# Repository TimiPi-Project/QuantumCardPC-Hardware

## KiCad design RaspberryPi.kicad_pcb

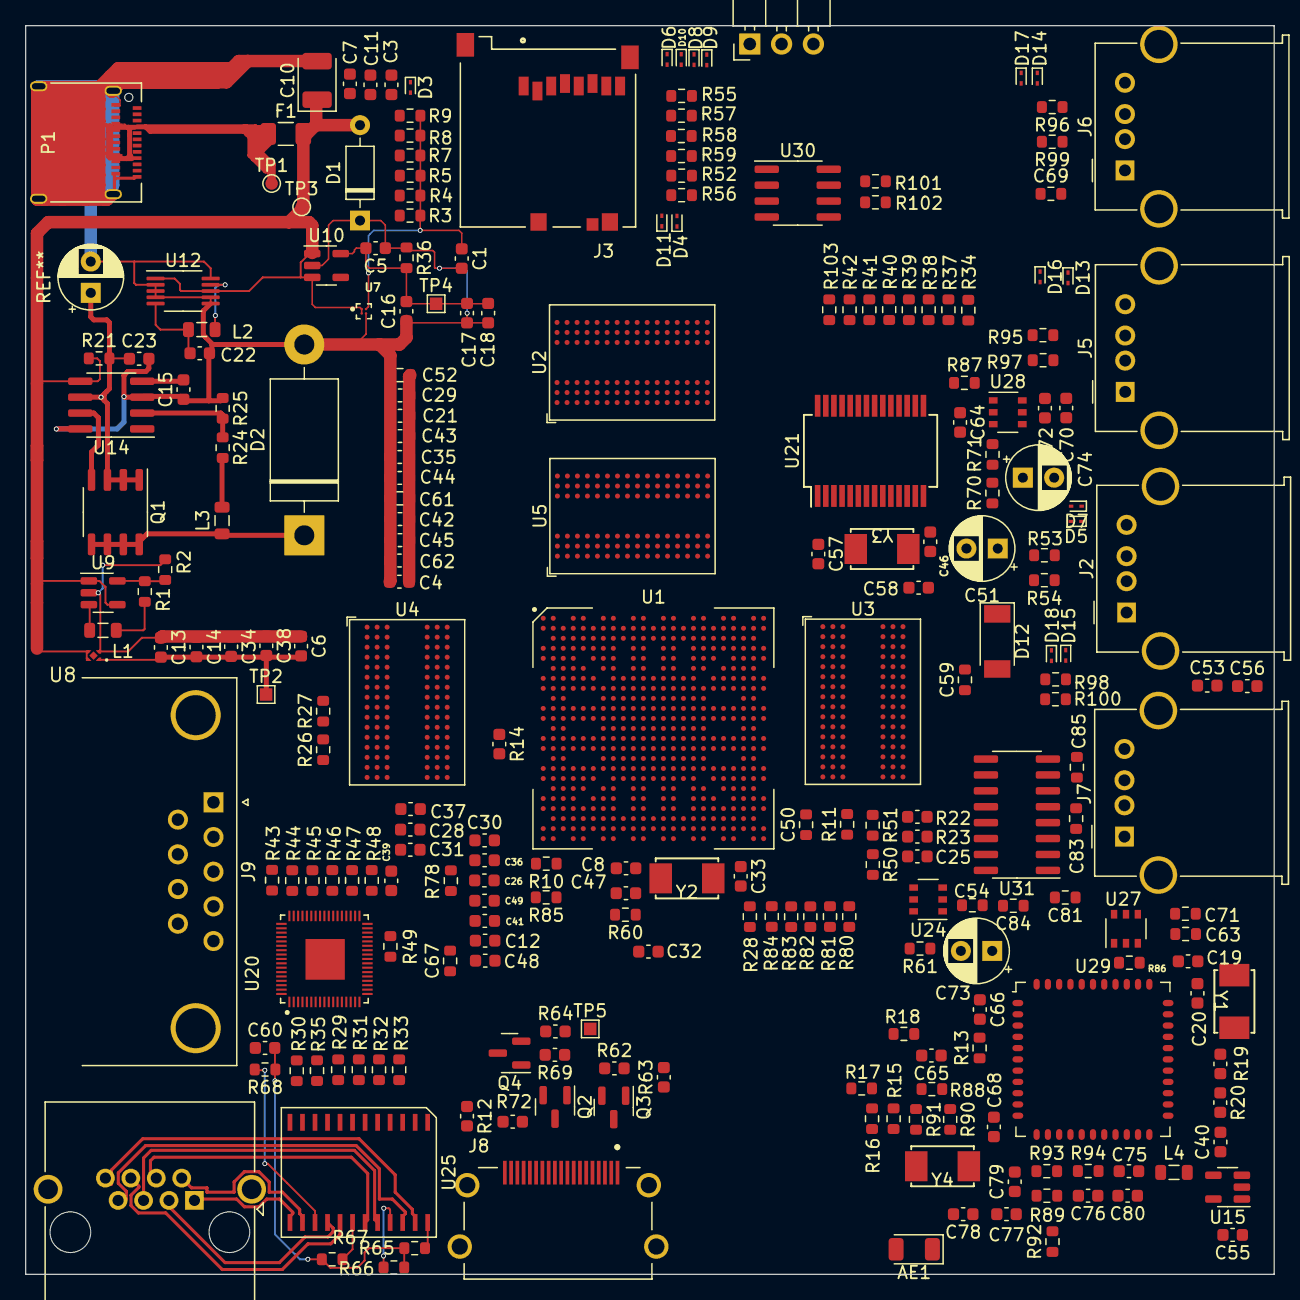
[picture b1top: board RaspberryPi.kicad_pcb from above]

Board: 4 copper layers, 99.7 x 99.7 mm, 244 parts (0 on the bottom side), 252 nets.

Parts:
AE1: Antenna; Johanson_2450AT18x100
C1, C4, C5, C6, C13, C17, C21, C23, C30, C31, C35, C36, C39, C40, C42, C43, C44, C45, C47, C49, C53, C64: 100nF; C_0603_1608Metric
C3, C34, C46, C48, C56: 1uF; C_0603_1608Metric
C7: 4.7uF; C_0603_1608Metric
C8, C18, C26, C28, C38, C55: 10nF; C_0603_1608Metric
C10: 47uF; CP_EIA-3528-21_Kemet-B
C11, C12, C16, C29, C62, C70: 10uF; C_0603_1608Metric
C14, C25, C41, C60: 1nF; C_0603_1608Metric
C15, C72: 0.1uF; C_0603_1608Metric
C19, C20, C57, C58: 22pF; C_0603_1608Metric
C22, C37: 22uF; C_0603_1608Metric
C32, C33: 12pF; C_0603_1608Metric
C50, C54, C63, C81, C83, C84, C85: 100nF; R_0603_1608Metric
C51, C73, C74: CP_Radial_D5.0mm_P2.50mm
C52, C59, C61, C69: 10uF; R_0603_1608Metric
C65, C68, C75, C76, C77, C78, C79, C80: 18pF; C_0603_1608Metric
C66: 10pF; C_0603_1608Metric
C67: 22pF; R_0603_1608Metric
C71: 0.1uF; R_0603_1608Metric
D1: SMBJ5.0A; D_DO-35_SOD27_P7.62mm_Horizontal
D2: 1N5820; D_DO-201AD_P15.24mm_Horizontal
D3, D4, D5, D6, D7, D8, D9, D10, D11, D13, D14, D15, D16, D17, D18: ESD9B5VL; D_SOD-923
D12: PMEG3030BEP; D_SOD-128
F1: 5A; Fuse_1206_3216Metric
J1: DBG1; PinHeader_1x03_P2.54mm_Horizontal
J2, J5, J6, J7: USB_A; USB_A_Molex_67643_Horizontal
J3: Micro_SD_Card_Det; MOLEX_47352-1001
J4: RJ45; RJ45_Amphenol_RJHSE5380
J8: HDMI_A; AMPHENOL_10029449-001RLF
J9: DB9_Male; DSUB-9_Male_Horizontal_P2.77x2.84mm_EdgePinOffset7.70mm_Hou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
L1: 2.2uH; L_0805_2012Metric
L2: 10uH; L_0805_2012Metric
L3: 47uH; L_0805_2012Metric
L4: 3.3uH; L_0805_2012Metric
P1: USB_C_Plug_USB2.0; USB_C_Receptacle_Amphenol_12401610E4-2A
Q1: Si9430; SO-8_3.9x4.9mm_P1.27mm
Q2, Q3, Q4: 2N7002; SOT-23
R1, R40: 100K; R_0603_1608Metric
R2: 120K; R_0603_1608Metric
R3, R4, R5, R7, R8, R9, R10, R13, R15, R16, R17, R18, R27, R34, R38, R39, R41, R42, R50, R60, R70, R71, R101: 10K; R_0603_1608Metric
R11: 133R; R_0603_1608Metric
R12, R22, R23: 1K; C_0603_1608Metric
R14: 1.62K; C_0603_1608Metric
R19, R62: 10K; C_0603_1608Metric
R20: 22R; C_0603_1608Metric
R21: 0.05R; R_0603_1608Metric
R24: 180K; R_0603_1608Metric
R25: 150K; R_0603_1608Metric
R26: 6.8K; R_0603_1608Metric
R28: 1M; R_0603_1608Metric
R29, R30, R31, R32, R33, R35, R44, R45, R46, R47, R49: 4K7; R_0603_1608Metric
R36: 510R; R_0603_1608Metric
R37: 680R; R_0603_1608Metric
R43: 2.49K; R_0603_1608Metric
R48: 1K5; R_0603_1608Metric
R51: 15K; R_0603_1608Metric
R52, R55, R56, R57, R58, R59, R89, R90, R91, R92, R93, R94: 22R; R_0603_1608Metric
R53, R54, R95, R96, R97, R98, R99, R100: 90; R_0603_1608Metric
R61, R86, R87: 20K; R_0603_1608Metric
R63, R64: 4.7K; C_0603_1608Metric
R65, R66, R67, R68: 75; R_0603_1608Metric
R69, R72: 1.5K; C_0603_1608Metric
R78, R80, R81, R82, R83, R84, R85: 22; R_0603_1608Metric
R88: 100R; R_0603_1608Metric
R102, R103: 2.2K; R_0603_1608Metric
TP1, TP3: +5; TestPoint_Pad_D1.0mm
TP2: 1V_USB; TestPoint_Pad_1.0x1.0mm
TP4: 1V8_USB; TestPoint_Pad_1.0x1.0mm
TP5: 3V3_IO; TestPoint_Pad_1.0x1.0mm
U1: RK3368; TFBGA453
U2, U3, U4, U5: MT41KxxxM16TW; BGA-96_9.0x13.0mm_Layout2x3x16_P0.8mm
U7: TPS7A21; BGA4N35P2X2_64X64X33
U8: TPS7A0310; SUP_TPS3831L30DQNR
U9: TLV62565-LibCool; SOT-23-5
U10: TPS72118; SOT-23-5
U12: TPS62052DGS; VSSOP-10_3x3mm_P0.5mm
U14: MAX1651; SOIC-8_3.9x4.9mm_P1.27mm
U15: SN74LVC1G14DBV; SOT-23-5
U20: RTL8211E-VB-CG; QFN35P700X700X80-69N
U21: GL852G; SSOP-28_5.3x10.2mm_P0.65mm
U24, U27, U28: MP65151DJ; TSOP-6_1.65x3.05mm_P0.95mm
U25: GST5009; SOIC-24
U29: AP6335
U30: AT24C16B; SOIC-8_3.9x4.9mm_P1.27mm
U31: MAX3232; SOIC-16_3.9x9.9mm_P1.27mm
Y1: 32.768kHz; OSC_5032
Y2: 24MHz; OSC_5032
Y3: 12MHz; OSC_5032
Y4: 37.4MHz; OSC_5032

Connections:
+1V0: C6.2, C12.2, C13.2, C14.2, C26.2, C30.2, C34.2, C36.2, C38.2, C41.2, C48.2, C49.2, TP2.1, U1.G13 (PLL_VDD_1), U1.N7, U1.R7, U1.V21, U1.W7, U1.W8, U1.Y8, U1.Y21, U8.1 (OUT), U20.3 (VDD10), U20.9 (VDD10), U20.28 (VDD10), U20.36 (VDD10), U20.40 (VDD10)
+1V1: L1.1, R1.2, U1.E18, U1.G8, U1.G10, U1.G12, U1.G14, U1.G16, U1.J17, U1.M17, U1.N8, U1.T16, U1.T17, U1.U9, U1.U10, U1.U11, U1.U12, U1.U13, U1.U14, U1.U15, U1.U16, U1.V10, U1.V11, U1.V13, U1.V14, U1.V16, U1.W10, U1.W11, U1.W13, U1.W14, U1.W16, U1.Y13, U1.Y14
+1V5: C22.2, L2.2, U12.5 (FB)
+1V8: C5.2, C16.2, C17.2, C18.2, R10.2, R36.2, TP4.1, U1.N6, U1.T7, U1.V20, U1.Y10, U10.5 (OUT)
+3.3VP: C1.1, R3.2, R4.2, R5.2, R7.2, R8.2, R9.2, U7.A2 (OUT)
+3V3: C4.2, C21.2, C29.2, C35.2, C39.2, C42.2, C43.2, C44.2, C45.2, C52.2, C61.2, C62.2, J3.4 (VDD), L3.2, Q2.1 (G), Q3.1 (G), Q4.1 (G), R13.2, R15.2, R16.2, R17.2, R18.2, R19.2, R24.2, R30.1, R34.2, R35.1, R39.1, R40.1, R41.1, R42.1, R44.2, R45.2, R46.2, R47.2, R48.2, R49.1, R62.2, R63.2, R64.2, R101.1, R102.1, R103.1, TP5.1, U1.K17, U1.P17, U1.T4, U1.T5, U1.T6, U15.5 (VCC), U20.6 (VDD33), U20.15 (VDD33), U20.21 (VDD33), U20.37 (VDD33), U20.38 (ENSWREG), U20.41 (VDD33), U20.44 (VDD33), U20.45 (VDD33), U21.1 (AVDD1), U21.5 (AVDD2), U21.10 (AVDD3), U21.16 (DVDD), U21.24 (V33), U24.1 (IN), U27.1 (IN), U28.1 (IN), U29.9 (VBat), U29.22 (VDDIO), U30.8 (VCC), U31.16 (VCC)
+5V: C3.1, C7.2, C10.1, C11.1, D1.2 (A), F1.2, J8.18 (+5V), R21.1, R50.2, R69.2, R72.2, TP3.1, U7.A1 (IN), U7.B1 (EN), U8.3 (EN), U8.4 (IN), U9.1 (EN), U9.4 (VIN), U10.1 (IN), U10.3 (EN), U12.1 (VIN), U12.8 (EN), U14.5 (V+)
/32K_IN: C40.2, R20.2, U1.AA9, U15.2, U15.4, U29.24 (LPO)
/A0: U1.A11 (A0), U2.N3 (A0), U3.N3 (A0), U4.N3 (A0), U5.N3 (A0)
/A1: U1.C12 (A1), U2.P7 (A1), U3.P7 (A1), U4.P7 (A1), U5.P7 (A1)
/A2: U1.B12 (A2), U2.P3 (A2), U3.P3 (A2), U4.P3 (A2), U5.P3 (A2)
/A3: U1.E13 (A3), U2.N2 (A3), U3.N2 (A3), U4.N2 (A3), U5.N2 (A3)
/A4: U1.C13 (A4), U2.P8 (A4), U3.P8 (A4), U4.P8 (A4), U5.P8 (A4)
/A5: U1.A14 (A5), U2.P2 (A5), U3.P2 (A5), U4.P2 (A5), U5.P2 (A5)
/A6: U1.B14 (A6), U2.R8 (A6), U3.R8 (A6), U4.R8 (A6), U5.R8 (A6)
/A7: U1.C14 (A7), U2.R2 (A7), U3.R2 (A7), U4.R2 (A7), U5.R2 (A7)
/A8: U1.D14 (A8), U2.T8 (A8), U3.T8 (A8), U4.T8 (A8), U5.T8 (A8)
/A9: U1.E14 (A9), U2.R3 (A9), U3.R3 (A9), U4.R3 (A9), U5.R3 (A9)
/A10: U1.C15 (A10), U2.L7 (A10/AP), U3.L7 (A10/AP), U4.L7 (A10/AP), U5.L7 (A10/AP)
/A11: U1.B15 (A11), U2.R7 (A11), U3.R7 (A11), U4.R7 (A11), U5.R7 (A11)
/A12: U1.D18 (A12), U2.N7 (A12/~BC), U3.N7 (A12/~BC), U4.N7 (A12/~BC), U5.N7 (A12/~BC)
/A13: U1.C16 (A13), U2.T3 (A13), U3.T3 (A13), U4.T3 (A13), U5.T3 (A13)
/A14: U1.B16 (A14), U2.T7 (A14), U3.T7 (A14), U4.T7 (A14), U5.T7 (A14)
/BA0: U1.D11 (BA0), U2.M2 (BA0), U3.M2 (BA0), U4.M2 (BA0), U5.M2 (BA0)
/BA1: U1.C11 (BA1), U2.N8 (BA1), U3.N8 (BA1), U4.N8 (BA1), U5.N8 (BA1)
/BA2: U1.B11 (BA2), U2.M3 (BA2), U3.M3 (BA2), U4.M3 (BA2), U5.M3 (BA2)
/CASN: U1.B10 (CASN), U2.K3 (~CAS), U3.K3 (~CAS), U4.K3 (~CAS), U5.K3 (~CAS)
/CEC: J8.13 (CEC), Q2.3 (D)
/CKE0: U1.C9 (CKE0), U2.K9 (CKE), U3.K9 (CKE), U4.K9 (CKE), U5.K9 (CKE)
/CLK: U1.B13 (DDRCLK), U2.J7 (CK), U3.J7 (CK), U4.J7 (CK), U5.J7 (CK)
/CLKN: U1.A13 (DDRCLKN), U2.K7 (~CK), U3.K7 (~CK), U4.K7 (~CK), U5.K7 (~CK)
/CS0N: U1.A8 (CS0N), U3.L2 (~CS), U5.L2 (~CS)
/CS1N: U1.B9 (CS1N), U2.L2 (~CS), U4.L2 (~CS)
/D0: U1.E22 (DQ0), U2.F7 (DQ1), U3.E3 (DQ0)
/D1: U1.D21 (DQ1), U3.F7 (DQ1)
/D2: U1.C22 (DQ2), U2.F8 (DQ3), U3.F2 (DQ2)
/D3: U1.D22 (DQ3), U2.F2 (DQ2), U3.F8 (DQ3)
/D4: U1.A23 (DQ4), U2.H7 (DQ7), U3.H3 (DQ4)
/D5: U1.B23 (DQ5), U3.H8 (DQ5)
/D6: U1.D23 (DQ6), U2.H8 (DQ5), U3.G2 (DQ6)
/D7: U1.E23 (DQ7), U2.H3 (DQ4), U3.H7 (DQ7)
/D8: U1.D6 (DQ8), U4.F7 (DQ1), U5.E3 (DQ0)
/D9: U1.C6 (DQ9), U4.E3 (DQ0), U5.F7 (DQ1)
/D10: U1.B6 (DQ10), U4.F8 (DQ3), U5.F2 (DQ2)
/D11: U1.E7 (DQ11), U4.F2 (DQ2), U5.F8 (DQ3)
/D12: U1.C7 (DQ12), U4.H7 (DQ7), U5.H3 (DQ4)
/D13: U1.E8 (DQ13), U4.G2 (DQ6), U5.H8 (DQ5)
/D14: U1.D8 (DQ14), U4.H8 (DQ5), U5.G2 (DQ6)
/D15: U1.C8 (DQ15), U4.H3 (DQ4), U5.H7 (DQ7)
/D16: U1.C18 (DQ16), U2.C3 (DQ9), U3.D7 (DQ8)
/D17: U1.B17 (DQ17), U2.D7 (DQ8), U3.C3 (DQ9)
/D18: U1.A17 (DQ18), U2.C2 (DQ11), U3.C8 (DQ10)
/D19: U1.A20 (DQ19), U2.C8 (DQ10), U3.C2 (DQ11)
/D20: U1.C19 (DQ20), U2.A3 (DQ15), U3.A7 (DQ12)
/D21: U1.B18 (DQ21), U2.B8 (DQ14), U3.A2 (DQ13)
/D22: U1.B20 (DQ22), U2.A2 (DQ13), U3.B8 (DQ14)
/D23: U1.B21 (DQ23), U2.A7 (DQ12), U3.A3 (DQ15)
/D24: U1.B2 (DQ24), U4.C3 (DQ9), U5.D7 (DQ8)
/D25: U1.B3 (DQ25), U4.D7 (DQ8), U5.C3 (DQ9)
/D26: U1.C3 (DQ26), U4.C2 (DQ11), U5.C8 (DQ10)
/D27: U1.C4 (DQ27), U4.C8 (DQ10), U5.C2 (DQ11)
/D28: U1.D5 (DQ28), U4.A3 (DQ15), U5.A7 (DQ12)
/D29: U1.C5 (DQ29), U4.B8 (DQ14), U5.A2 (DQ13)
/D30: U1.B5 (DQ30), U4.A2 (DQ13), U5.B8 (DQ14)
/D31: U1.A5 (DQ31), U4.A7 (DQ12), U5.A3 (DQ15)
/DDCSCL: J8.15 (SCL), Q3.3 (D), R69.1
/DDCSDA: J8.16 (SDA), Q4.3 (D), R72.1
/DDRPWR: C28.2, C31.2, C37.2, R22.2, U1.E16 (VDD9), U1.E17 (VDD10), U1.F7 (VDD1), U1.F8 (VDD2), U1.F10 (VDD3), U1.F11 (VDD4), U1.F13 (VDD5), U1.F14 (VDD6), U1.F16 (VDD7), U1.F17 (VDD8), U2.A1 (VDDQ), U2.A8 (VDDQ), U2.B2 (VDD), U2.C1 (VDDQ), U2.C9 (VDDQ), U2.D2 (VDDQ), U2.D9 (VDD), U2.E9 (VDDQ), U2.F1 (VDDQ), U2.G7 (VDD), U2.H1 (VREFDQ), U2.H2 (VDDQ), U2.H9 (VDDQ), U2.K2 (VDD), U2.K8 (VDD), U2.M8 (VREFCA), U2.N1 (VDD), U2.N9 (VDD), U2.R1 (VDD), U2.R9 (VDD), U3.A1 (VDDQ), U3.A8 (VDDQ), U3.B2 (VDD), U3.C1 (VDDQ), U3.C9 (VDDQ), U3.D2 (VDDQ), U3.D9 (VDD), U3.E9 (VDDQ), U3.F1 (VDDQ), U3.G7 (VDD), U3.H1 (VREFDQ), U3.H2 (VDDQ), U3.H9 (VDDQ), U3.K2 (VDD), U3.K8 (VDD), U3.M8 (VREFCA), U3.N1 (VDD), U3.N9 (VDD), U3.R1 (VDD), U3.R9 (VDD), U4.A1 (VDDQ), U4.A8 (VDDQ), U4.B2 (VDD), U4.C1 (VDDQ), U4.C9 (VDDQ), U4.D2 (VDDQ), U4.D9 (VDD), U4.E9 (VDDQ), U4.F1 (VDDQ), U4.G7 (VDD), U4.H1 (VREFDQ), U4.H2 (VDDQ), U4.H9 (VDDQ), U4.K2 (VDD), U4.K8 (VDD), U4.M8 (VREFCA), U4.N1 (VDD), U4.N9 (VDD), U4.R1 (VDD), U4.R9 (VDD), U5.A1 (VDDQ), U5.A8 (VDDQ), U5.B2 (VDD), U5.C1 (VDDQ), U5.C9 (VDDQ), U5.D2 (VDDQ), U5.D9 (VDD), U5.E9 (VDDQ), U5.F1 (VDDQ), U5.G7 (VDD), U5.H1 (VREFDQ), U5.H2 (VDDQ), U5.H9 (VDDQ), U5.K2 (VDD), U5.K8 (VDD), U5.M8 (VREFCA), U5.N1 (VDD), U5.N9 (VDD), U5.R1 (VDD), U5.R9 (VDD)
/DDR_RST: U1.E11 (RESETN), U2.T2 (~RESET), U3.T2 (~RESET), U4.T2 (~RESET), U5.T2 (~RESET)
/DM0: U1.D20 (DM0), U2.E7 (LDM), U3.E7 (LDM)
/DM1: U1.E6 (DM1), U4.E7 (LDM), U5.E7 (LDM)
/DM2: U1.C20 (DM2), U2.D3 (UDM), U3.D3 (UDM)
/DM3: U1.A2 (DM3), U4.D3 (UDM), U5.D3 (UDM)
/DQS0M: U1.A22 (DQS0N), U2.G3 (~LDQS), U3.G3 (~LDQS)
/DQS0P: U1.B22 (DQS0), U2.F3 (LDQS), U3.F3 (LDQS)
/DQS1M: U1.A7 (DQS1N), U4.G3 (~LDQS), U5.G3 (~LDQS)
/DQS1P: U1.B7 (DQS1), U4.F3 (LDQS), U5.F3 (LDQS)
/DQS2M: U1.A19 (DQS2N), U2.B7 (~UDQS), U3.B7 (~UDQS)
/DQS2P: U1.B19 (DQS2), U2.C7 (UDQS), U3.C7 (UDQS)
/DQS3M: U1.A4 (DQS3N), U4.B7 (~UDQS), U5.B7 (~UDQS)
/DQS3P: U1.B4 (DQS3), U4.C7 (UDQS), U5.C7 (UDQS)
/HDMICEC: Q2.2 (S), R62.1, U1.U23
/HDMITXC+: J8.10 (CK+), U1.AB1
/HDMITXC-: J8.12 (CK-), U1.AC1
/HDMITXD0+: J8.7 (D0+), U1.AB2
/HDMITXD0-: J8.9 (D0-), U1.AC2
/HDMITXD1+: J8.4 (D1+), U1.AB4
/HDMITXD1-: J8.6 (D1-), U1.AC4
/HDMITXD2+: J8.1 (D2+), U1.AB5
/HDMITXD2-: J8.3 (D2-), U1.AC5
/HDMI_HPD: J8.19 (HPD), R12.2
/HOST1_D+: U1.AB23, U21.26 (DP0)
/HOST1_D-: U1.AC23, U21.25 (DM0)
/HOST_PWR1: C70.2, C72.2, C74.1, J5.1 (VBUS), U28.6 (OUT)
/HOST_PWR2: C69.2, C71.2, C73.1, J6.1 (VBUS), J7.1 (VBUS), U27.6 (OUT)
/HOST_VBus: R70.1, R71.1, U1.AA8
/HUB_D2+: R96.2, U21.3 (DP2)
/HUB_D2-: R99.2, U21.2 (DM2)
/HUB_D3+: R95.2, U21.9 (DP3)
/HUB_D3-: R97.2, U21.8 (DM3)
/I2C2_SCL: R102.2, U1.F20, U30.6 (SCL)
/I2C2_SDA: R103.2, U1.E20, U30.5 (SDA)
/I2C5_SCL_HDMI: Q3.2 (S), R63.1, U1.T23
/I2C5_SDA_HDMI: Q4.2 (S), R64.1, U1.T22
/MAC_MDIO: R48.1, U20.31 (MAC_MDIO)
/MDI0+: U20.1 (MDI0+), U25.12 (TD4-)
/MDI0-: U20.2 (MDI0-), U25.11 (TD4+)
/MDI1+: U20.4 (MDI1+), U25.9 (TD3-)
/MDI1-: U20.5 (MDI1-), U25.8 (TD3+)
/MDI2+: U20.7 (MDI2+), U25.6 (TD2-)
/MDI2-: U20.8 (MDI2-), U25.5 (TD2+)
/MDI3+: U20.10 (MDI3+), U25.3 (TD1-)
/MDI3-: U20.11 (MDI3-), U25.2 (TD1+)
/ODT0: U1.D17 (ODT0), U3.K1 (ODT), U5.K1 (ODT)
/ODT1: U1.C17 (ODT1), U2.K1 (ODT), U4.K1 (ODT)
/OTGVDD: C59.2, D12.2 (A), U24.6 (OUT)
/OTG_D+: R53.2, U1.AB22
/OTG_D-: R54.2, U1.AC22
/OTG_DET: C50.2, R50.1, R51.2, U1.AA21
/OTG_VBus: R60.1, U1.AB14
/PHY_CLKOUT125: C67.2, R78.2, U20.46 (CLK125)
/PHY_INT: R35.2, U20.20 (INTB)
/PHY_PMEB: R49.2, U20.33 (PHY_PMEB)
/PHY_RXD0: R30.2, U20.14 (RXD0)
/PHY_RXD1: R31.2, U20.16 (RXD1)
/PHY_RXD2: R32.2, U20.17 (RXD2)
/PHY_RXD3: R33.2, U20.18 (RXD3)
/PHY_RXDV: R29.2, U20.13 (RXCTL)
/PHY_TXCLK: R80.2, U20.22 (TXC)
/PHY_TXD0: R44.1, R81.2, U20.23 (TXD0)
/PHY_TXD1: R45.1, R82.2, U20.24 (TXD1)
/PHY_TXD2: R46.1, R83.2, U20.25 (PHY_TXD2)
/PHY_TXD3: R47.1, R84.2, U20.26 (PHY_TXD3)
/PHY_TXEN: R85.2, U20.27 (PHY_TXEN)
/RASN: U1.A10 (RASN), U2.J3 (~RAS), U3.J3 (~RAS), U4.J3 (~RAS), U5.J3 (~RAS)
/RECOVER: C8.2, R10.1, U1.AC11
/RSET: R43.1, U20.39 (RSET)
/RST: C47.1, U1.AC8
/SDIO0_CLK: R92.1, U1.L19
/SDIO0_CMD: R18.1, R91.1, U1.L21
/SDIO0_D0: R13.1, R93.1, U1.M22
/SDIO0_D1: R15.1, R94.1, U1.N20
/SDIO0_D2: R16.1, R89.1, U1.N23
/SDIO0_D3: R17.1, R90.1, U1.L20
/SDMMC_CLK: R57.1, U1.N22
/SDMMC_CMD: R8.1, R55.1, U1.N19
/SDMMC_D0: J1.2, R3.1, R56.1, U1.P18
/SDMMC_D1: J1.1, R4.1, R52.1, U1.P22
/SDMMC_D2: R5.1, R59.1, U1.R22
/SDMMC_D3: R7.1, R58.1, U1.P23
/SDMMC_DET: D3.2 (A2), J3.SW, R9.1, U1.N21
/UART0_CTS: U1.K21, U29.41 (UART_RTS)
/UART0_RX: U1.K22, U29.42 (UART_TXD)
/UART0_TX: U1.K19, U29.43 (UART_RXD)
/UART1_CTS: U1.V5, U31.9 (R2OUT)
/UART1_RTS: U1.Y6, U31.10 (T2IN)
/UART1_RX: U1.U5, U31.12 (R1OUT)
/UART1_TX: U1.Y4, U31.11 (T1IN)
/VREF_DDR: C25.2, R22.1, R23.2
/WEN: U1.C10 (WEN), U2.L3 (~WE), U3.L3 (~WE), U4.L3 (~WE), U5.L3 (~WE)
/XIN: C57.1, U21.6 (XTAL), Y3.2
/XOU: C58.1, U21.7 (XTAL2), Y3.1
GND: C1.2, C3.2, C4.1, C5.1, C6.1, C7.1, C8.1, C10.2, C11.2, C12.1, C13.1, C14.1, C15.1, C16.1, C17.1, C18.1, C19.1, C20.1, C21.1, C22.1, C23.2, C25.1, C26.1, C28.1, C29.1, C30.1, C31.1, C32.1, C33.1, C34.1, C35.1, C36.1, C37.1, C38.1, C39.1, C40.1, C41.1, C42.1, C43.1, C44.1, C45.1, C46.1, C47.2, C48.1, C49.1, C50.1, C51.2, C52.1, C53.1, C54.1, C55.1, C56.1, C57.2, C58.2, C59.1, C60.1, C61.1, C62.1, C63.1, C64.1, C65.1, C67.1, C68.1, C69.1, C70.1, C71.1, C72.1, C73.2, C74.2, C75.1, C76.1, C77.1, C78.1, C79.1, C80.1, C84.2, C85.2, D1.1 (K), D2.2 (A), D3.1 (A1), D4.1 (A1), D5.1 (A1), D6.1 (A1), D7.1 (A1), D8.1 (A1), D9.1 (A1), D10.1 (A1), D11.1 (A1), D13.1 (A1), D14.1 (A1), D15.1 (A1), D16.1 (A1), D17.1 (A1), D18.1 (A1), J1.3, J2.4 (GND), J2.5 (Shield), J3.6 (VSS), J5.4 (GND), J5.5 (Shield), J6.4 (GND), J6.5 (Shield), J7.4 (GND), J7.5 (Shield), J8.2 (D2S), J8.5 (D1S), J8.8 (D0S), J8.11 (CKS), J8.17 (GND), J9.5, P1.A1 (GND), P1.A12 (GND), P1.B1 (GND), P1.B12 (GND), P1.S1 (SHIELD), R2.1, R11.2, R14.2, R23.1, R25.1, R26.1, R29.1, R31.1, R32.1, R33.1, R36.1, R37.1, R38.1, R43.2, R51.1, R61.1, R86.1, R87.1, U1.AA4, U1.AA5, U1.AA10, U1.AA20, U1.AA22, U1.AB3, U1.AB6, U1.AB9, U1.AB21, U1.C2, U1.C21, U1.D4, U1.D7, U1.D10, U1.D13, U1.D16, U1.D19, U1.E21, U1.F2, U1.G9, U1.G11, U1.G15, U1.H3, U1.H8, U1.H9, U1.H10, U1.H11, U1.H12, U1.H13, U1.H14, U1.H15, U1.H16, U1.J8, U1.J9, U1.J10, U1.J11, U1.J12, U1.J13, U1.J14, U1.J15, U1.J16, U1.K3, U1.K8, U1.K9, U1.K10, U1.K11, U1.K12, U1.K13, U1.K14, U1.K15, U1.K16, U1.L3, U1.L8, U1.L9, U1.L10, U1.L11, U1.L12, U1.L13, U1.L14, U1.L15, U1.L16, U1.M8, U1.M9, U1.M10, U1.M11, U1.M12, U1.M13, U1.M14, U1.M15, U1.M16, U1.N3, U1.N9, U1.N10, U1.N11, U1.N12, U1.N13, U1.N14, U1.N15, U1.N16, U1.P3, U1.P7, U1.P8, U1.P9, U1.P10, U1.P11, U1.P12, U1.P13, U1.P14, U1.P15, U1.P16, U1.P20, U1.R8, U1.R9, U1.R10, U1.R11, U1.R12, U1.R13, U1.R14, U1.R15, U1.R16, U1.T3, U1.T9, U1.T10, U1.T11, U1.T12, U1.T13, U1.T14, U1.T15, U1.U3, U1.U8, U1.U20, U1.V7, U1.V8, U1.W3, U1.Y3, U1.Y22, U2.A9 (VSS), U2.B1 (VSSQ), U2.B3 (VSS), U2.B9 (VSSQ), U2.D1 (VSSQ), U2.D8 (VSSQ), U2.E1 (VSS), U2.E2 (VSSQ), U2.E8 (VSSQ), U2.F9 (VSSQ), U2.G1 (VSSQ), U2.G8 (VSS), U2.G9 (VSSQ), U2.J2 (VSS), U2.J8 (VSS), U2.M1 (VSS), U2.M9 (VSS), U2.P1 (VSS), U2.P9 (VSS), U2.T1 (VSS), U2.T9 (VSS), U3.A9 (VSS), U3.B1 (VSSQ), U3.B3 (VSS), U3.B9 (VSSQ), U3.D1 (VSSQ), U3.D8 (VSSQ), U3.E1 (VSS), U3.E2 (VSSQ), U3.E8 (VSSQ), U3.F9 (VSSQ), U3.G1 (VSSQ), U3.G8 (VSS), U3.G9 (VSSQ), U3.J2 (VSS), U3.J8 (VSS), U3.M1 (VSS), U3.M9 (VSS), U3.P1 (VSS), U3.P9 (VSS), U3.T1 (VSS), U3.T9 (VSS), U4.A9 (VSS), U4.B1 (VSSQ), U4.B3 (VSS), U4.B9 (VSSQ), U4.D1 (VSSQ), U4.D8 (VSSQ), U4.E1 (VSS), U4.E2 (VSSQ), U4.E8 (VSSQ), U4.F9 (VSSQ), U4.G1 (VSSQ), U4.G8 (VSS), U4.G9 (VSSQ), U4.J2 (VSS), U4.J8 (VSS), U4.M1 (VSS), U4.M9 (VSS), U4.P1 (VSS), U4.P9 (VSS), U4.T1 (VSS), U4.T9 (VSS), U5.A9 (VSS), U5.B1 (VSSQ), U5.B3 (VSS), U5.B9 (VSSQ), U5.D1 (VSSQ), U5.D8 (VSSQ), U5.E1 (VSS), U5.E2 (VSSQ), U5.E8 (VSSQ), U5.F9 (VSSQ), U5.G1 (VSSQ), U5.G8 (VSS), U5.G9 (VSSQ), U5.J2 (VSS), U5.J8 (VSS), U5.M1 (VSS), U5.M9 (VSS), U5.P1 (VSS), U5.P9 (VSS), U5.T1 (VSS), U5.T9 (VSS), U7.B2 (GND), U8.2 (GND), U9.2 (GND), U10.2 (GND), U12.2 (LBO), U12.3 (GND), U12.4 (PG), U12.6 (LBI), U12.7 (SYNC), U12.10 (PGND), U14.3 (SHDN), U14.8 (GND), U15.3 (GND), U21.15 (GND), U24.2 (GND), U27.2 (GND), U28.2 (GND), U29.1 (GND1), U29.30 (VDD_TCXO), U30.4 (GND), U31.15 (GND)
unnamed: AE1.1 (A), C66.1
unnamed: C19.2, R19.1, R20.1, Y1.2
unnamed: C20.2, Y1.1
unnamed: C60.2, R65.1, R66.1, R67.1, R68.1
unnamed: C65.2, R88.1, Y4.1
unnamed: D2.1 (K), L3.1, Q1.5, Q1.6, Q1.7, Q1.8
unnamed: D4.2 (A2), J3.8 (DAT1), R52.2
unnamed: D5.2 (A2), J2.2 (D-), R54.1
unnamed: D6.2 (A2), J3.7 (DAT0), R56.2
unnamed: D7.2 (A2), J2.3 (D+), R53.1
unnamed: D8.2 (A2), J3.5 (CLK), R57.2
unnamed: D9.2 (A2), J3.3 (CMD), R55.2
unnamed: D10.2 (A2), J3.2 (DAT3/CD), R58.2
unnamed: D11.2 (A2), J3.1 (DAT2), R59.2
unnamed: C51.1, C53.2, C56.2, D12.1 (K), J2.1 (VBUS)
unnamed: D13.2 (A2), J5.3 (D+), R95.1
unnamed: D14.2 (A2), J6.3 (D+), R96.1
unnamed: D15.2 (A2), J7.3 (D+), R98.1
unnamed: D16.2 (A2), J5.2 (D-), R97.1
unnamed: D17.2 (A2), J6.2 (D-), R99.1
unnamed: D18.2 (A2), J7.2 (D-), R100.1
unnamed: F1.1, P1.A4 (VBUS), P1.A9 (VBUS), P1.B4 (VBUS), P1.B9 (VBUS), TP1.1
unnamed: Q1.4, U14.7 (EXT)
unnamed: C23.1, Q1.1 (G), Q1.2 (S), Q1.3 (D), R21.2, U14.6 (CS)
unnamed: R11.1, U1.R17
unnamed: R1.1, R2.2, U9.5 (FB)
unnamed: L1.2, U9.3 (SW)
unnamed: R12.1, U1.N4
unnamed: R14.1, U1.N5
unnamed: L2.1, U12.9 (SW)
unnamed: R24.1, R25.2, U14.2 (FB)
unnamed: C15.2, U14.4 (REF)
unnamed: R26.2, R27.1
unnamed: C32.2, R28.2, U1.AC10, Y2.1
unnamed: C33.2, R28.1, U1.AB10, Y2.2
unnamed: R41.2, U21.21 (OVCUR1)
unnamed: R42.2, U21.19 (OVCUR2)
unnamed: R40.2, U21.18 (PGANG)
unnamed: R39.2, U21.17 (PSELF)
unnamed: C46.2, R34.1, U21.13 (RESET#)
unnamed: R37.2, U21.4 (RREF)
unnamed: R38.2, U21.14 (TEST/SCL)
unnamed: C54.2, R60.2, U24.3 (EN), U24.4 (FLAG)
unnamed: R61.2, U24.5 (ILIM)
unnamed: R65.2, U25.24 (TCT1)
unnamed: C55.2, U25.1 (TCT1), U25.4 (TCT2), U25.7 (TCT3), U25.10 (TCT4)
unnamed: R66.2, U25.21 (TCT2)
unnamed: R67.2, U25.18 (TCT3)
unnamed: R68.2, U25.15 (TCT4)
unnamed: R78.1, U1.U18
unnamed: R81.1, U1.T18
unnamed: R82.1, U1.U19
unnamed: R83.1, U1.T20
unnamed: R85.1, U1.V19
unnamed: R84.1, U1.T19
unnamed: C63.2, R70.2, U27.3 (EN), U27.4 (FLAG)
unnamed: R86.2, U27.5 (ILIM)
unnamed: C64.2, R71.2, U28.3 (EN), U28.4 (FLAG)
unnamed: R87.2, U28.5 (ILIM)
unnamed: C66.2, U29.2 (ANT)
unnamed: C76.2, R93.2, U29.18 (SDIO_DATA_0)
unnamed: C75.2, R94.2, U29.19 (SDIO_DATA_1)
unnamed: C80.2, R89.2, U29.14 (SDIO_DATA_2)
unnamed: C79.2, R90.2, U29.15 (SDIO_DATA_3)
unnamed: C77.2, R92.2, U29.17 (SDIO_DATA_CLK)
unnamed: C78.2, R91.2, U29.16 (SDIO_DATA_CMD)
unnamed: L4.2, U29.23 (VIN_LDO)
unnamed: L4.1, U29.21 (VIN_LDO_OUT)
unnamed: C68.2, U29.11 (VTAL_OUT), Y4.2
unnamed: R88.2, U29.10 (XTAL_IN)
unnamed: R101.2, U30.7 (WP)
unnamed: C81.2, U31.1 (C1+)
unnamed: C81.1, U31.3 (C1-)
unnamed: C83.1, U31.4 (C2+)
unnamed: C83.2, U31.5 (C2-)
unnamed: J9.2, U31.13 (R1IN)
unnamed: J9.8, U31.8 (R2IN)
unnamed: J9.3, U31.14 (T1OUT)
unnamed: J9.7, U31.7 (T2OUT)
unnamed: C84.1, U31.2 (VS+)
unnamed: C85.1, U31.6 (VS-)
TD1+: J4.8, U25.23 (TD1+)
TD1-: J4.7, U25.22 (TD1-)
TD2+: J4.5, U25.20 (TD2+)
TD2-: J4.4, U25.19 (TD2-)
TD3+: J4.6, U25.17 (TD3+)
TD3-: J4.3, U25.16 (TD3-)
TD4+: J4.2, U25.14 (TD4+)
TD4-: J4.1, U25.13 (TD4-)

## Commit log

2022-03-21 同步第一次初始化提交
2022-03-21 内存完工
2022-03-23 点位图完成了一片内存
2022-03-23 有人来帮忙布三根线吗
2022-03-23 算了 我搞完了
2022-03-23 漏了一点
2022-05-16 5-16 PC
2022-05-16 5-17 phone
2022-05-17 原理图完工
2022-05-17 Plot PDF
2022-05-17 指派封装1/3
